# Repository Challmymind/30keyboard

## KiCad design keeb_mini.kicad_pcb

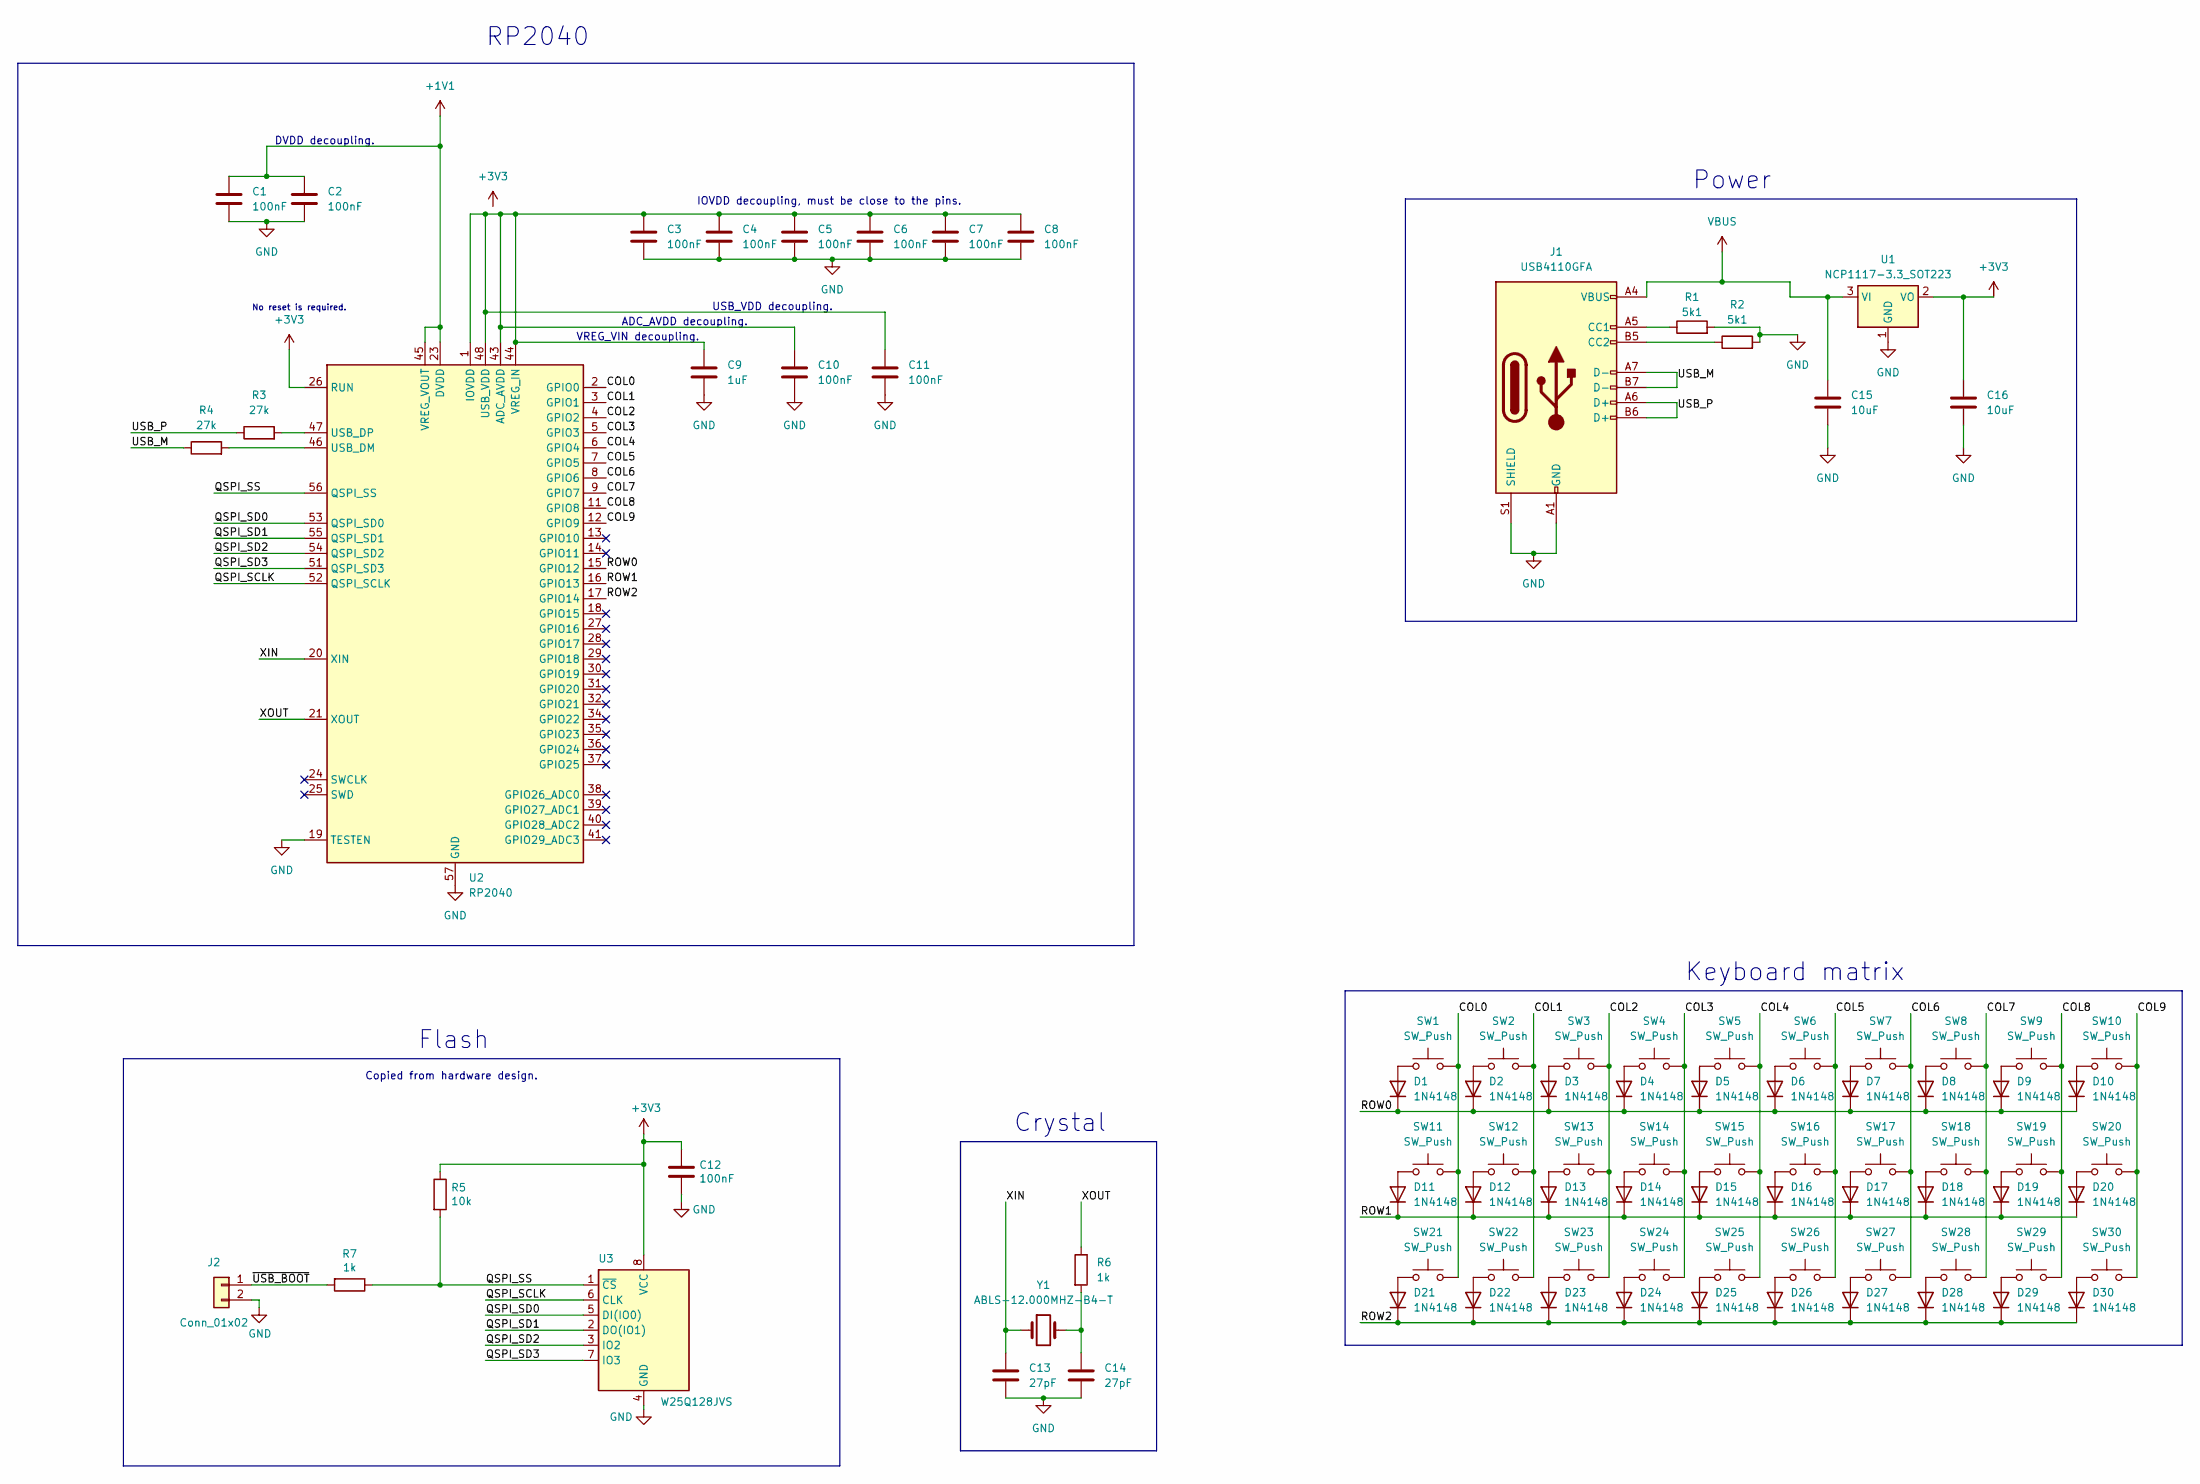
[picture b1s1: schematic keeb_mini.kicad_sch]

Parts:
C1, C2, C3, C4, C5, C6, C7, C8, C10, C11, C12: 100nF; C_0805_2012Metric
C9: 1uF; C_0805_2012Metric
C13, C14: 27pF; C_0805_2012Metric
C15, C16: 10uF; C_0805_2012Metric
D1, D2, D3, D4, D5, D6, D7, D8, D9, D10, D11, D12, D13, D14, D15, D16, D17, D18, D19, D20, D21, D22, D23, D24, D25, D26, D27, D28, D29, D30: 1N4148; D_SOD-523
J1: USB4110GFA; USB_C_Receptacle_GCT_USB4110
J2: Conn_01x02; PinHeader_1x02_P2.54mm_Vertical
R1, R2: 5k1; R_0805_2012Metric
R3, R4: 27k; R_0805_2012Metric
R5: 10k; R_0805_2012Metric
R6, R7: 1k; R_0805_2012Metric
SW1, SW2, SW3, SW4, SW5, SW6, SW7, SW8, SW9, SW10, SW11, SW12, SW13, SW14, SW15, SW16, SW17, SW18, SW19, SW20, SW21, SW22, SW23, SW24, SW25, SW26, SW27, SW28, SW29, SW30: SW_Push; MX-Solderable-1U
U1: NCP1117-3.3_SOT223; SOT-223-3_TabPin2
U2: RP2040; QFN-56-1EP_7x7mm_P0.4mm_EP3.2x3.2mm
U3: W25Q128JVS; SOIC-8_5.23x5.23mm_P1.27mm
Y1: ABLS-12.000MHZ-B4-T; Crystal_SMD_HC49-SD

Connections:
+1V1: C1.1, C2.1, U2.23 (DVDD), U2.45 (VREG_VOUT), U2.50 (DVDD)
+3V3: C12.1, C16.1, R5.1, U1.2 (VO), U2.26 (RUN), U3.8 (VCC)
/COL0: SW1.2, SW11.2, SW21.2, U2.2 (GPIO0)
/COL1: SW2.2, SW12.2, SW22.2, U2.3 (GPIO1)
/COL2: SW3.2, SW13.2, SW23.2, U2.4 (GPIO2)
/COL3: SW4.2, SW14.2, SW24.2, U2.5 (GPIO3)
/COL4: SW5.2, SW15.2, SW25.2, U2.6 (GPIO4)
/COL5: SW6.2, SW16.2, SW26.2, U2.7 (GPIO5)
/COL6: SW7.2, SW17.2, SW27.2, U2.8 (GPIO6)
/COL7: SW8.2, SW18.2, SW28.2, U2.9 (GPIO7)
/COL8: SW9.2, SW19.2, SW29.2, U2.11 (GPIO8)
/COL9: SW10.2, SW20.2, SW30.2, U2.12 (GPIO9)
/QSPI_SCLK: U2.52 (QSPI_SCLK), U3.6 (CLK)
/QSPI_SD0: U2.53 (QSPI_SD0), U3.5 (DI(IO0))
/QSPI_SD1: U2.55 (QSPI_SD1), U3.2 (DO(IO1))
/QSPI_SD2: U2.54 (QSPI_SD2), U3.3 (IO2)
/QSPI_SD3: U2.51 (QSPI_SD3), U3.7 (IO3)
/QSPI_SS: R5.2, R7.1, U2.56 (QSPI_SS), U3.1 (~CS)
/ROW0: D1.1 (K), D2.1 (K), D3.1 (K), D4.1 (K), D5.1 (K), D6.1 (K), D7.1 (K), D8.1 (K), D9.1 (K), D10.1 (K), U2.15 (GPIO12)
/ROW1: D11.1 (K), D12.1 (K), D13.1 (K), D14.1 (K), D15.1 (K), D16.1 (K), D17.1 (K), D18.1 (K), D19.1 (K), D20.1 (K), U2.16 (GPIO13)
/ROW2: D21.1 (K), D22.1 (K), D23.1 (K), D24.1 (K), D25.1 (K), D26.1 (K), D27.1 (K), D28.1 (K), D29.1 (K), D30.1 (K), U2.17 (GPIO14)
/USB_M: J1.A7 (D-), J1.B7 (D-), R4.1
/USB_P: J1.A6 (D+), J1.B6 (D+), R3.1
/XIN: C13.1, U2.20 (XIN), Y1.1
/XOUT: R6.1, U2.21 (XOUT)
/~USB_BOOT: J2.1, R7.2
GND: C1.2, C2.2, C3.2, C4.2, C5.2, C6.2, C7.2, C8.2, C9.2, C10.2, C11.2, C12.2, C13.2, C14.2, C15.2, C16.2, J1.A1 (GND), J1.A12 (GND), J1.B1 (GND), J1.B12 (GND), J1.S1 (SHIELD), J2.2, R1.2, R2.2, U1.1 (GND), U2.19 (TESTEN), U2.57 (GND), U3.4 (GND)
unnamed: C14.1, R6.2, Y1.2
unnamed: D1.2 (A), SW1.1
unnamed: D2.2 (A), SW2.1
unnamed: D3.2 (A), SW3.1
unnamed: D4.2 (A), SW4.1
unnamed: D5.2 (A), SW5.1
unnamed: D6.2 (A), SW6.1
unnamed: D7.2 (A), SW7.1
unnamed: D8.2 (A), SW8.1
unnamed: D9.2 (A), SW9.1
unnamed: D10.2 (A), SW10.1
unnamed: D11.2 (A), SW11.1
unnamed: D12.2 (A), SW12.1
unnamed: D13.2 (A), SW13.1
unnamed: D14.2 (A), SW14.1
unnamed: D15.2 (A), SW15.1
unnamed: D16.2 (A), SW16.1
unnamed: D17.2 (A), SW17.1
unnamed: D18.2 (A), SW18.1
unnamed: D19.2 (A), SW19.1
unnamed: D20.2 (A), SW20.1
unnamed: D21.2 (A), SW21.1
unnamed: D22.2 (A), SW22.1
unnamed: D23.2 (A), SW23.1
unnamed: D24.2 (A), SW24.1
unnamed: D25.2 (A), SW25.1
unnamed: D26.2 (A), SW26.1
unnamed: D27.2 (A), SW27.1
unnamed: D28.2 (A), SW28.1
unnamed: D29.2 (A), SW29.1
unnamed: D30.2 (A), SW30.1
unnamed: J1.A5 (CC1), R1.1
unnamed: J1.B5 (CC2), R2.1
unnamed: C3.1, C4.1, C5.1, C6.1, C7.1, C8.1, C9.1, C10.1, C11.1, U2.1 (IOVDD), U2.10 (IOVDD), U2.22 (IOVDD), U2.33 (IOVDD), U2.42 (IOVDD), U2.43 (ADC_AVDD), U2.44 (VREG_IN), U2.48 (USB_VDD), U2.49 (IOVDD)
unnamed: R4.2, U2.46 (USB_DM)
unnamed: R3.2, U2.47 (USB_DP)
VBUS: C15.1, J1.A4 (VBUS), J1.A9 (VBUS), J1.B4 (VBUS), J1.B9 (VBUS), U1.3 (VI)

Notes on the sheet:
Power
Keyboard matrix
VREG_VIN decoupling.
USB_VDD decoupling.
Crystal
No reset is required.
DVDD decoupling.
RP2040
ADC_AVDD decoupling.
Copied from hardware design.
IOVDD decoupling, must be close to the pins.
Flash

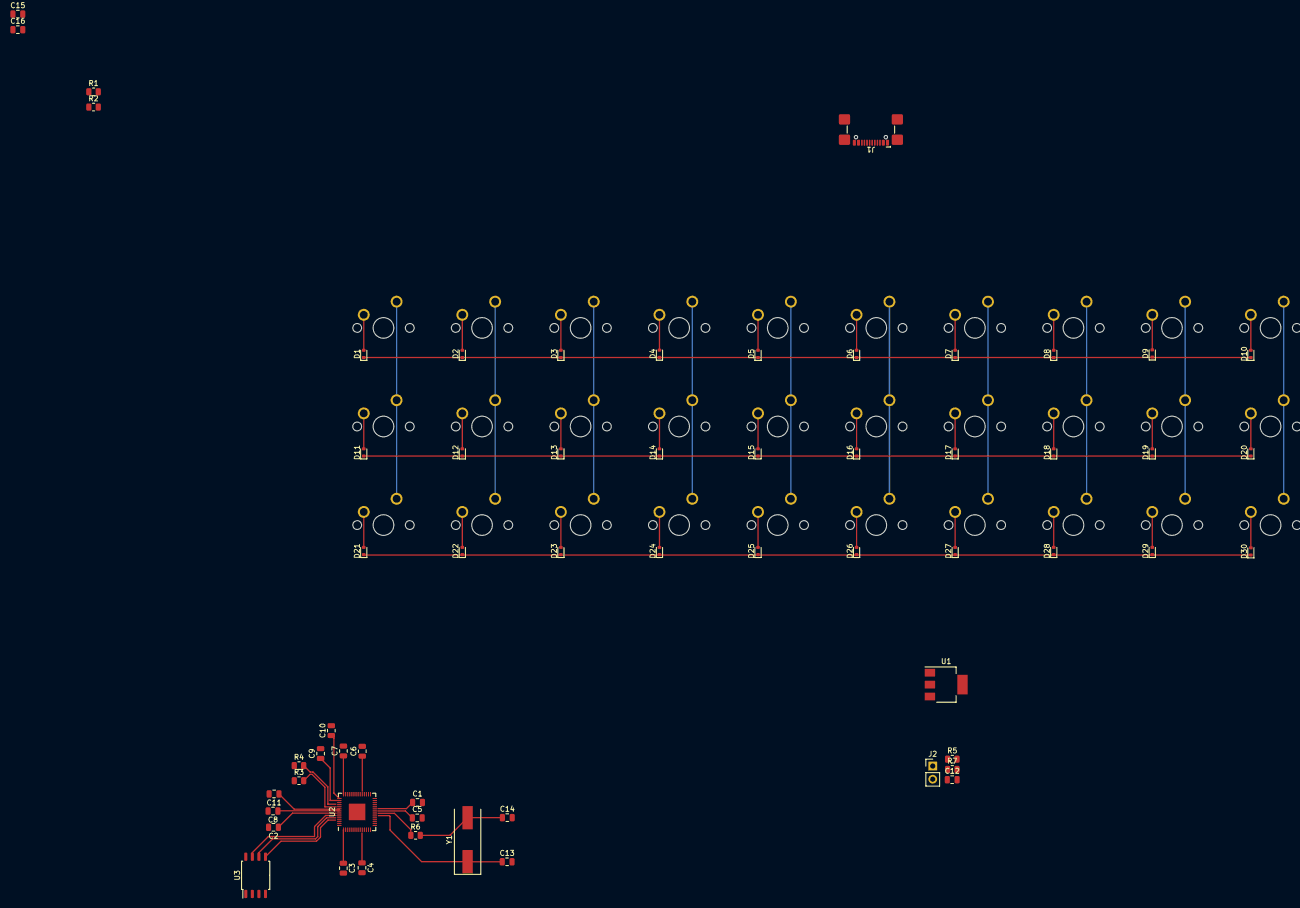
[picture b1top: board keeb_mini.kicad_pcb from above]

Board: 2 copper layers, 89 parts (0 on the bottom side), 64 nets.

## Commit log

2024-03-13 Created boilerplate for future keyboard work
2024-03-15 Started PCB making, encountered issues with routing
